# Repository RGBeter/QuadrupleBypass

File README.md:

# Quadruple Bypass
Update to the triple bypass mod for the genesis with on board mono audio, composite and S-Video generation for all models, ensuring complete functionality of the din for all genesis systems.

Also adds a ZIF connector for a future ribbon cable design to greatly simplify installation

(instructions pending, same as 3bp install except composite and mono must also be isolated from the din, and the subcarrier line must be routed to the 4bp)
### When routing the subcarrier line, make sure it's a shielded coaxial cable or twisted pair to prevent jailbars

## Model 1 Installation Guides
[Model 1 - VA1-VA6]
[Model 1 - VA7]
## Model 2 Installation Guides
[Model 2 - VA0-1.8]

[Model 2 - VA2]

[Model 2 - VA2.3]

[Model 2 - VA3]

[Model 2 - VA4]

## Model 3 Installation Guides
[Model 3 - VA1]

[Model 3 - VA2]

## Sega CDX
[CDX]

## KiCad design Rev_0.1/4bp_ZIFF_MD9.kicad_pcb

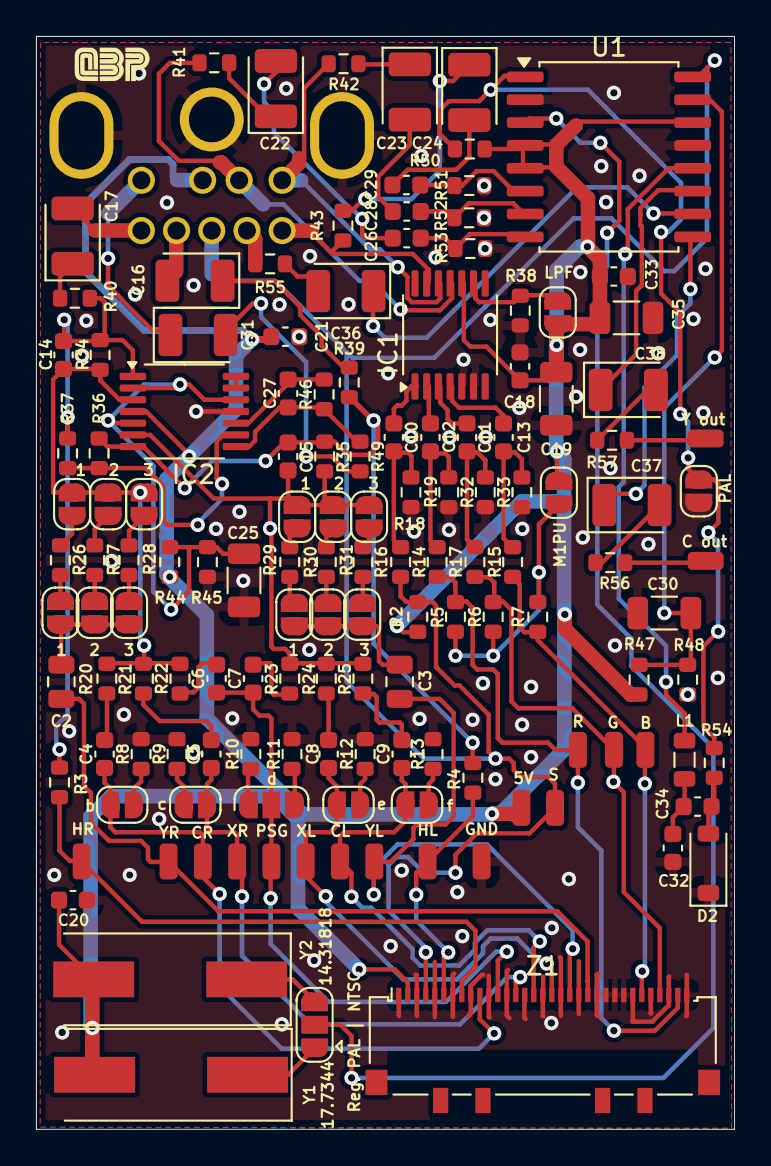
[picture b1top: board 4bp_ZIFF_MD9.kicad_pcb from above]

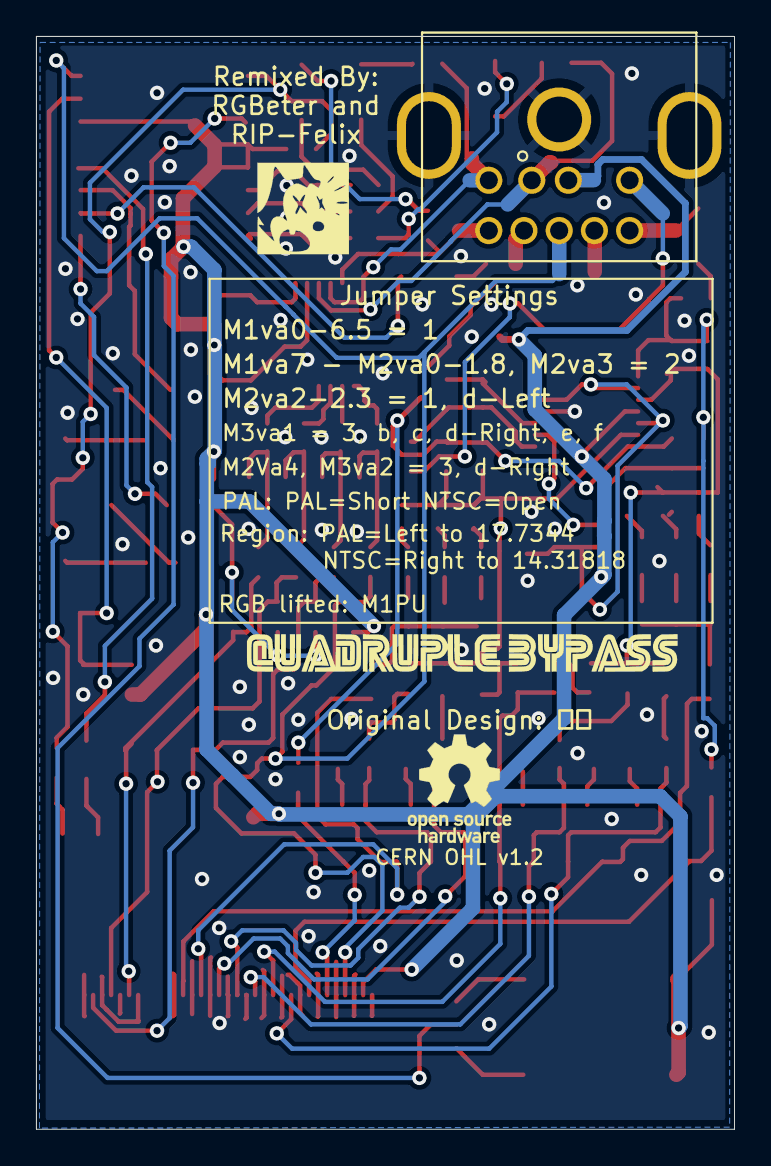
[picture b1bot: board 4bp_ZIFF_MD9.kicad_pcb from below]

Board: 2 copper layers, 38.8 x 60.7 mm, 142 parts (2 on the bottom side), 91 nets.

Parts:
B1: SMD_Conn_01x01; SolderWirePad_1x01_SMD_1x2mm
B_1: SolderJumper_2_Open; SolderJumper-2_P1.3mm_Open_RoundedPad1.0x1.5mm
C1: SolderJumper_2_Open; SolderJumper-2_P1.3mm_Open_RoundedPad1.0x1.5mm
C2, C3: 10u; C_0805_2012Metric
C4, C5, C6, C7, C8, C9: 1u; C_0603_1608Metric
C10, C11, C12, C13, C18, C20, C21, C26, C28, C29, C33: 0.1u; C_0603_1608Metric
C14, C15: 150p; C_0603_1608Metric
C16, C17, C31: 47u; CP_EIA-3528-15_AVX-H
C19, C25, C30, C35: 10u; C_1206_3216Metric
C22, C23, C24, C36, C37, C38: 220u; CP_EIA-3528-15_AVX-H
C27: 1nf; C_0603_1608Metric
C32: 18p; C_0603_1608Metric
C34: 9p; C_0603_1608Metric
CL1: SMD_Conn_01x01; SolderWirePad_1x01_SMD_1x2mm
CN1: MD-90SM_MD2; MD90SM-MD2
CR1: SMD_Conn_01x01; SolderWirePad_1x01_SMD_1x2mm
D1: SolderJumper_3_Open; SolderJumper-3_P1.3mm_Open_RoundedPad1.0x1.5mm
D2: 1N4148W; D_SOD-123
E1: SolderJumper_2_Open; SolderJumper-2_P1.3mm_Open_RoundedPad1.0x1.5mm
F1: SolderJumper_2_Open; SolderJumper-2_P1.3mm_Open_RoundedPad1.0x1.5mm
G1: SMD_Conn_01x01; SolderWirePad_1x01_SMD_1x2mm
GND1: SMD_Conn_01x01; SolderWirePad_1x01_SMD_1x2mm
IC1, IC2: MC33204; TSSOP-14_4.4x5mm_P0.65mm
J1, J2, J5, J6: SMD_Conn_01x01; SolderWirePad_1x01_SMD_1x2mm
J3: SolderJumper_3_Open; SolderJumper-3_P1.3mm_Open_RoundedPad1.0x1.5mm
J4: SolderJumper_2_Open; SolderJumper-2_P1.3mm_Open_RoundedPad1.0x1.5mm
L1: 68u; L_0805_2012Metric
LPF1: SolderJumper_2_Open; SolderJumper-2_P1.3mm_Open_RoundedPad1.0x1.5mm
M1PU1: SolderJumper_2_Open; SolderJumper-2_P1.3mm_Open_RoundedPad1.0x1.5mm
P1: SMD_Conn_01x01; SolderWirePad_1x01_SMD_1x2mm
R1: SMD_Conn_01x01; SolderWirePad_1x01_SMD_1x2mm
R2, R11: 2.2k; R_0603_1608Metric
R3, R4, R27, R30: 100k; R_0603_1608Metric
R5, R6, R7, R14, R15, R16, R17, R38: 5.62k; R_0603_1608Metric
R8, R9, R12, R13, R41, R42, R43, R51, R52, R53, R55, R56, R57: 75; R_0603_1608Metric
R10: 750; R_0603_1608Metric
R18, R19, R32, R33: 1k; R_0603_1608Metric
R20, R21, R22, R23, R24, R25: 210k; R_0603_1608Metric
R26, R29, R36, R37, R44, R45, R47, R48, R50: 10k; R_0603_1608Metric
R28, R31: 130k; R_0603_1608Metric
R34, R35: 300k; R_0603_1608Metric
R39, R40, R49: 330; R_0603_1608Metric
R46: 5.6k; R_0603_1608Metric
R54: 470; R_0603_1608Metric
Ref**: LOGO; QBP_LOGO
Ref**#2: LOGO; 4bp_LOGO
S1: SMD_Conn_01x01; SolderWirePad_1x01_SMD_1x2mm
U1: AD725; SOIC-16W_7.5x10.3mm_P1.27mm
UNK5V1: SMD_Conn_01x01; SolderWirePad_1x01_SMD_1x2mm
XL1: SMD_Conn_01x01; SolderWirePad_1x01_SMD_1x2mm
XR1: SMD_Conn_01x01; SolderWirePad_1x01_SMD_1x2mm
Y1: HCM4917734475ABJT; Crystal_SMD_HC49-SD
Y2: HCM4914318180BBKT; Crystal_SMD_HC49-SD
YL1: SMD_Conn_01x01; SolderWirePad_1x01_SMD_1x2mm
YL2, YL3, YL4, YL5, YL6, YL7: SolderJumper_2_Open; SolderJumper-2_P1.3mm_Open_RoundedPad1.0x1.5mm
YR1: SMD_Conn_01x01; SolderWirePad_1x01_SMD_1x2mm
YR2, YR3, YR4, YR5, YR6, YR7: SolderJumper_2_Open; SolderJumper-2_P1.3mm_Open_RoundedPad1.0x1.5mm
Z1: Conn_01x33_Pin; Molex_502244-3330_1x33-1MP_P0.5mm_Horizontal

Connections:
2V5: C25.1, IC2.2 (-), IC2.5 (+), IC2.12 (+), R44.1, R45.2
2V5_IC3: C30.1, R47.1, R48.2, U1.15 (VSYNC)
+5V: C18.1, C19.1, C20.1, C21.1, C33.1, C35.1, CN1.2 (5V), IC2.4 (V+), LPF1.2 (B), M1PU1.1 (A), R2.2, R44.2, R47.2, R50.2, U1.4 (AVCC), U1.5 (CE), U1.14 (DVCC), UNK5V1.1, Y1.2, Y2.2, Z1.2
/AUD-L: C15.2, IC2.6 (-), R23.2, R24.2, R25.2, R35.1, YL5.2 (B), YL6.2 (B), YL7.2 (B)
/AUD-R: C14.2, IC2.3 (+), R20.2, R21.2, R22.2, R34.1, YR5.2 (B), YR6.2 (B), YR7.2 (B)
/B-IN: B1.1, R7.1, R15.1, Z1.28
/CL: C9.2, CL1.1, F1.1 (A), Z1.16
/CR: B_1.1 (A), C4.2, CR1.1, Z1.10
/G-IN: G1.1, R6.1, R17.1, Z1.30
/HL: J2.1, R4.1, Z1.6
/HR: J1.1, R3.1, Z1.8
/OUT1: C14.1, IC2.1, R3.2, R34.2, R36.1, R40.1
/OUT2: C15.1, IC2.7, R4.2, R35.2, R37.2, R39.1
/OUT3: C27.1, IC2.8, R46.2, R49.1
/PSG: C6.2, C7.2, D1.2 (C), P1.1, Z1.12
/R-IN: R1.1, R5.1, R14.1, Z1.32
/SL: C16.2, CN1.8 (SL)
/SR: C17.2, CN1.9 (SR)
/STDSEL: J4.2 (B), R50.1, R54.2, U1.1 (NTSC/PAL)
/SYNC-TTL: CN1.5 (SYNC), R2.1, R16.1, S1.1, U1.16 (HSYNC), Z1.4
/XL: C8.2, E1.1 (A), XL1.1, Z1.18
/XR: C1.1 (A), C5.2, XR1.1, Z1.14
/YL: C3.2, YL1.1, Z1.20
/YR: C2.2, YR1.1, Z1.22
B-OUT: CN1.1 (B), R41.1
CLK: J3.2 (C), U1.3 (4FSC_CLK)
CVBS: CN1.4 (CVBS), R55.1
G-OUT: CN1.3 (G), R42.1
GND: C18.2, C19.2, C20.2, C21.2, C25.2, C30.2, C32.2, C33.2, C35.2, CN1.S1 (RTN), CN1.S2 (RTN), CN1.S3 (RTN), D2.1 (K), GND1.1, IC2.11 (V-), J4.1 (A), R8.2, R9.2, R10.2, R11.2, R12.2, R13.2, R18.1, R19.1, R32.1, R33.1, R38.1, R45.1, R48.1, R51.1, R52.1, R53.1, U1.2 (AGND), U1.13 (DGND), Z1.1, Z1.3, Z1.5, Z1.7, Z1.9, Z1.11, Z1.13, Z1.15, Z1.17, Z1.19, Z1.21, Z1.23, Z1.24, Z1.25, Z1.26, Z1.27, Z1.29, Z1.31, Z1.33
unnamed: B_1.2 (B), R8.1
unnamed: C1.2 (B), R9.1
unnamed: C4.1, R20.1
unnamed: C5.1, R21.1
unnamed: C6.1, R22.1
unnamed: C7.1, R23.1
unnamed: C8.1, R24.1
unnamed: C9.1, R25.1
unnamed: C10.2, R16.2, R18.2
unnamed: C11.2, R17.2, R32.2
unnamed: C12.2, R14.2, R19.2
unnamed: C13.2, R15.2, R33.2
unnamed: C16.1, R39.2
unnamed: C17.1, R40.2
unnamed: C22.1, R41.2
unnamed: C22.2, C26.2
unnamed: C23.1, R42.2
unnamed: C23.2, C28.2
unnamed: C24.1, R43.2
unnamed: C24.2, C29.2
unnamed: C31.2, R49.2
unnamed: C32.1, C34.2, L1.2
unnamed: C36.2, R55.2
unnamed: C37.2, R56.2
unnamed: C38.2, R57.2
unnamed: C31.1, CN1.6 (MONO)
unnamed: D1.1 (A), R10.1
unnamed: D1.3 (B), R11.1
unnamed: C34.1, D2.2 (A), R54.1
unnamed: E1.2 (B), R12.1
unnamed: F1.2 (B), R13.1
unnamed: LPF1.1 (A), R38.2
unnamed: C27.2, IC2.10 (+), R46.1
unnamed: IC2.9 (-), R36.2, R37.1
unnamed: IC2.13 (-), IC2.14
unnamed: J3.1 (A), Y1.1
unnamed: J3.3 (B), Y2.1
unnamed: J5.1, R56.1
unnamed: J6.1, R57.1
unnamed: M1PU1.2 (B), R5.2, R6.2, R7.2
unnamed: C26.1, R53.2, U1.8 (BLUE)
unnamed: C37.1, U1.9 (CHROM_OUT)
unnamed: C36.1, U1.10 (CVBS_OUT)
unnamed: C28.1, R52.2, U1.7 (GREEN)
unnamed: C38.1, U1.11 (LUM_OUT)
unnamed: C29.1, R51.2, U1.6 (RED)
unnamed: L1.1, U1.12 (TRAP)
unnamed: C3.1, YL2.1 (A), YL3.1 (A), YL4.1 (A)
unnamed: R29.1, YL2.2 (B)
unnamed: R30.1, YL3.2 (B)
unnamed: R31.1, YL4.2 (B)
unnamed: R29.2, YL5.1 (A)
unnamed: R30.2, YL6.1 (A)
unnamed: R31.2, YL7.1 (A)
unnamed: C2.1, YR2.1 (A), YR3.1 (A), YR4.1 (A)
unnamed: R26.1, YR2.2 (B)
unnamed: R27.1, YR3.2 (B)
unnamed: R28.1, YR4.2 (B)
unnamed: R26.2, YR5.1 (A)
unnamed: R27.2, YR6.1 (A)
unnamed: R28.2, YR7.1 (A)
R-OUT: CN1.7 (R), R43.1

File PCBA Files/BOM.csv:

Comment,Designator,Footprint,JLCPCB Part #
SolderJumper_2_Open,B2,Jumper:SolderJumper-2_P1.3mm_Open_RoundedPad1.0x1.5mm,
0.1u,C1,Capacitor_SMD:C_0603_1608Metric,
SolderJumper_2_Open,C2,Jumper:SolderJumper-2_P1.3mm_Open_RoundedPad1.0x1.5mm,
10u,C3,Capacitor_SMD:C_0805_2012Metric,
10u,C4,Capacitor_SMD:C_0805_2012Metric,
1u,C5,Capacitor_SMD:C_0603_1608Metric,
1u,C6,Capacitor_SMD:C_0603_1608Metric,
1u,C7,Capacitor_SMD:C_0603_1608Metric,
1u,C8,Capacitor_SMD:C_0603_1608Metric,
1u,C9,Capacitor_SMD:C_0603_1608Metric,
1u,C10,Capacitor_SMD:C_0603_1608Metric,
0.1u,C11,Capacitor_SMD:C_0603_1608Metric,
0.1u,C12,Capacitor_SMD:C_0603_1608Metric,
0.1u,C13,Capacitor_SMD:C_0603_1608Metric,
0.1u,C14,Capacitor_SMD:C_0603_1608Metric,
150p,C15,Capacitor_SMD:C_0603_1608Metric,
150p,C16,Capacitor_SMD:C_0603_1608Metric,
47u,C17,Capacitor_Tantalum_SMD:CP_EIA-3528-15_AVX-H,
47u,C18,Capacitor_Tantalum_SMD:CP_EIA-3528-15_AVX-H,
0.1u,C19,Capacitor_SMD:C_0603_1608Metric,
10u,C20,Capacitor_SMD:C_1206_3216Metric,
0.1u,C21,Capacitor_SMD:C_0603_1608Metric,
220u,C22,Capacitor_Tantalum_SMD:CP_EIA-3528-15_AVX-H,
220u,C23,Capacitor_Tantalum_SMD:CP_EIA-3528-15_AVX-H,
220u,C24,Capacitor_Tantalum_SMD:CP_EIA-3528-15_AVX-H,
10u,C25,Capacitor_SMD:C_1206_3216Metric,
0.1u,C26,Capacitor_SMD:C_0603_1608Metric,
1nf,C27,Capacitor_SMD:C_0603_1608Metric,
0.1u,C28,Capacitor_SMD:C_0603_1608Metric,
0.1u,C29,Capacitor_SMD:C_0603_1608Metric,
10u,C30,Capacitor_SMD:C_1206_3216Metric,
47u,C31,Capacitor_Tantalum_SMD:CP_EIA-3528-15_AVX-H,
220u,C32,Capacitor_Tantalum_SMD:CP_EIA-3528-15_AVX-H,
220u,C33,Capacitor_Tantalum_SMD:CP_EIA-3528-15_AVX-H,
0.1u,C34,Capacitor_SMD:C_0603_1608Metric,
220u,C35,Capacitor_Tantalum_SMD:CP_EIA-3528-15_AVX-H,
10u,C36,Capacitor_SMD:C_1206_3216Metric,
MD-90SM_MD2,CN1,MyLibrary:MD90SM-MD2,
SolderJumper_3_Open,D1,Jumper:SolderJumper-3_P1.3mm_Open_RoundedPad1.0x1.5mm,
SolderJumper_2_Open,E1,Jumper:SolderJumper-2_P1.3mm_Open_RoundedPad1.0x1.5mm,
SolderJumper_2_Open,F1,Jumper:SolderJumper-2_P1.3mm_Open_RoundedPad1.0x1.5mm,
THS7374IPWR,IC1,Package_SO:TSSOP-14_4.4x5mm_P0.65mm,
TL974,IC2,Package_SO:SOIC-14_3.9x8.7mm_P1.27mm,
AD724,IC3,Package_SO:SOIC-16W_7.5x10.3mm_P1.27mm,
SolderJumper_2_Open,J3,Jumper:SolderJumper-2_P1.3mm_Open_RoundedPad1.0x1.5mm,
SolderJumper_2_Open,LPF1,Jumper:SolderJumper-2_P1.3mm_Open_RoundedPad1.0x1.5mm,
SolderJumper_2_Open,M1PU1,Jumper:SolderJumper-2_P1.3mm_Open_RoundedPad1.0x1.5mm,
2.2k,R2,Resistor_SMD:R_0603_1608Metric,
100k,R3,Resistor_SMD:R_0603_1608Metric,
100k,R4,Resistor_SMD:R_0603_1608Metric,
5.62k,R5,Resistor_SMD:R_0603_1608Metric,
5.62k,R6,Resistor_SMD:R_0603_1608Metric,
5.62k,R7,Resistor_SMD:R_0603_1608Metric,
75,R8,Resistor_SMD:R_0603_1608Metric,
75,R9,Resistor_SMD:R_0603_1608Metric,
750,R10,Resistor_SMD:R_0603_1608Metric,
2.2k,R11,Resistor_SMD:R_0603_1608Metric,
75,R12,Resistor_SMD:R_0603_1608Metric,
75,R13,Resistor_SMD:R_0603_1608Metric,
5.62k,R14,Resistor_SMD:R_0603_1608Metric,
5.62k,R15,Resistor_SMD:R_0603_1608Metric,
5.62k,R16,Resistor_SMD:R_0603_1608Metric,
5.62k,R17,Resistor_SMD:R_0603_1608Metric,
1k,R18,Resistor_SMD:R_0603_1608Metric,
1k,R19,Resistor_SMD:R_0603_1608Metric,
210k,R20,Resistor_SMD:R_0603_1608Metric,
210k,R21,Resistor_SMD:R_0603_1608Metric,
210k,R22,Resistor_SMD:R_0603_1608Metric,
210k,R23,Resistor_SMD:R_0603_1608Metric,
210k,R24,Resistor_SMD:R_0603_1608Metric,
210k,R25,Resistor_SMD:R_0603_1608Metric,
10k,R26,Resistor_SMD:R_0603_1608Metric,
100k,R27,Resistor_SMD:R_0603_1608Metric,
130k,R28,Resistor_SMD:R_0603_1608Metric,
10k,R29,Resistor_SMD:R_0603_1608Metric,
100k,R30,Resistor_SMD:R_0603_1608Metric,
130k,R31,Resistor_SMD:R_0603_1608Metric,
1k,R32,Resistor_SMD:R_0603_1608Metric,
1k,R33,Resistor_SMD:R_0603_1608Metric,
300k,R34,Resistor_SMD:R_0603_1608Metric,
300k,R35,Resistor_SMD:R_0603_1608Metric,
10k,R36,Resistor_SMD:R_0603_1608Metric,
10k,R37,Resistor_SMD:R_0603_1608Metric,
5.62k,R38,Resistor_SMD:R_0603_1608Metric,
330,R39,Resistor_SMD:R_0603_1608Metric,
330,R40,Resistor_SMD:R_0603_1608Metric,
75,R41,Resistor_SMD:R_0603_1608Metric,
75,R42,Resistor_SMD:R_0603_1608Metric,
75,R43,Resistor_SMD:R_0603_1608Metric,
10k,R44,Resistor_SMD:R_0603_1608Metric,
10k,R45,Resistor_SMD:R_0603_1608Metric,
5.5k,R46,Resistor_SMD:R_0603_1608Metric,
10k,R47,Resistor_SMD:R_0603_1608Metric,
10k,R48,Resistor_SMD:R_0603_1608Metric,
330,R49,Resistor_SMD:R_0603_1608Metric,
75,R50,Resistor_SMD:R_0603_1608Metric,
75,R51,Resistor_SMD:R_0603_1608Metric,
75,R52,Resistor_SMD:R_0603_1608Metric,
10k,R53,Resistor_SMD:R_0603_1608Metric,
75,R54,Resistor_SMD:R_0603_1608Metric,
75,R55,Resistor_SMD:R_0603_1608Metric,
75,R56,Resistor_SMD:R_0603_1608Metric,
SolderJumper_2_Open,YL2,Jumper:SolderJumper-2_P1.3mm_Open_RoundedPad1.0x1.5mm,
SolderJumper_2_Open,YL3,Jumper:SolderJumper-2_P1.3mm_Open_RoundedPad1.0x1.5mm,
SolderJumper_2_Open,YL4,Jumper:SolderJumper-2_P1.3mm_Open_RoundedPad1.0x1.5mm,
SolderJumper_2_Open,YR2,Jumper:SolderJumper-2_P1.3mm_Open_RoundedPad1.0x1.5mm,
SolderJumper_2_Open,YR3,Jumper:SolderJumper-2_P1.3mm_Open_RoundedPad1.0x1.5mm,
SolderJumper_2_Open,YR4,Jumper:SolderJumper-2_P1.3mm_Open_RoundedPad1.0x1.5mm,
Conn_01x33_Pin,Z1,Connector_FFC-FPC:Molex_502244-3330_1x33-1MP_P0.5mm_Horizontal,

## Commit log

2025-02-12 Updated README, removed old files
2025-02-12 File cleanup and prep
2025-02-24 Create folders
2025-02-24 4BP minor trace changes. added BOM, POS, and Gerbers. Still need TSSOP for the quad amp.
2025-03-01 Create placeholderfile
2025-03-04 0.1a Prototype sent to PCBA
2025-03-10 Added 2nd set of jumbers for resistor isolation

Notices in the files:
Rev_0.1/4bp_ZIFF_MD9.kicad_pcb:
CERN OHL v1.2
Licensed under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
